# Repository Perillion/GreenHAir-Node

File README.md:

# GreenHAir Node

A Bluetooth Low Energy (BLE) Node based on the Nordic Semiconductor nRF54L series. Designed for environmental monitoring and efficient data transmission.

## Features

*   **Core:** Powered by the Nordic nRF54L series for ultra-low power consumption.
*   **Connectivity:** Bluetooth Low Energy (BLE) for reliable wireless communication.
*   **Modular Design:** Separate schematics for MCU, PSU, and Sensors for easy customization.
*   **Power Supply:** Optimized power management unit (`psu.kicad_sch`) powered by a CR2032 coin cell.
*   **Sensing:** Equipped with an AS7341DLG Lux sensor (I2C) for precise light measurement (`sensor.kicad_sch`).
*   **RF Performance:** Includes various antenna footprint options for optimal range.

## Hardware Structure

The project is divided into several KiCad schematics:

*   `GreenHAir_Node.kicad_sch`: Top-level hierarchy.
*   `mcu.kicad_sch`: Microcontroller and core logic.
*   `psu.kicad_sch`: Power supply and management.
*   `sensor.kicad_sch`: Sensor interfaces and components.

## Installation & Fabrication

### 1. PCB Fabrication
Generate the Gerber files from `GreenHAir_Node.kicad_pcb` and send them to your preferred PCB manufacturer.

### 2. Assembly
Follow the BOM (Bill of Materials) generated from the schematic to source and solder components.

### 3. Firmware
(Add instructions for flashing the nRF54L chip here)

## Customization

### Sensors
Currently populated with an AS7341DLG spectral sensor. The `sensor.kicad_sch` sheet allows for easy modification or expansion of the sensor array.

### Antenna
The design supports multiple antenna configurations found in the `libs/RF_Antenna.pretty` library.

## Contributing

Contributions are welcome! Please feel free to submit a Pull Request.

1.  Fork the repository
2.  Create your feature branch (`git checkout -b feature/AmazingFeature`)
3.  Commit your changes (`git commit -m 'Add some AmazingFeature'`)
4.  Push to the branch (`git push origin feature/AmazingFeature`)
5.  Open a Pull Request

## License

Distributed under the MIT License. See `LICENSE` for more information.

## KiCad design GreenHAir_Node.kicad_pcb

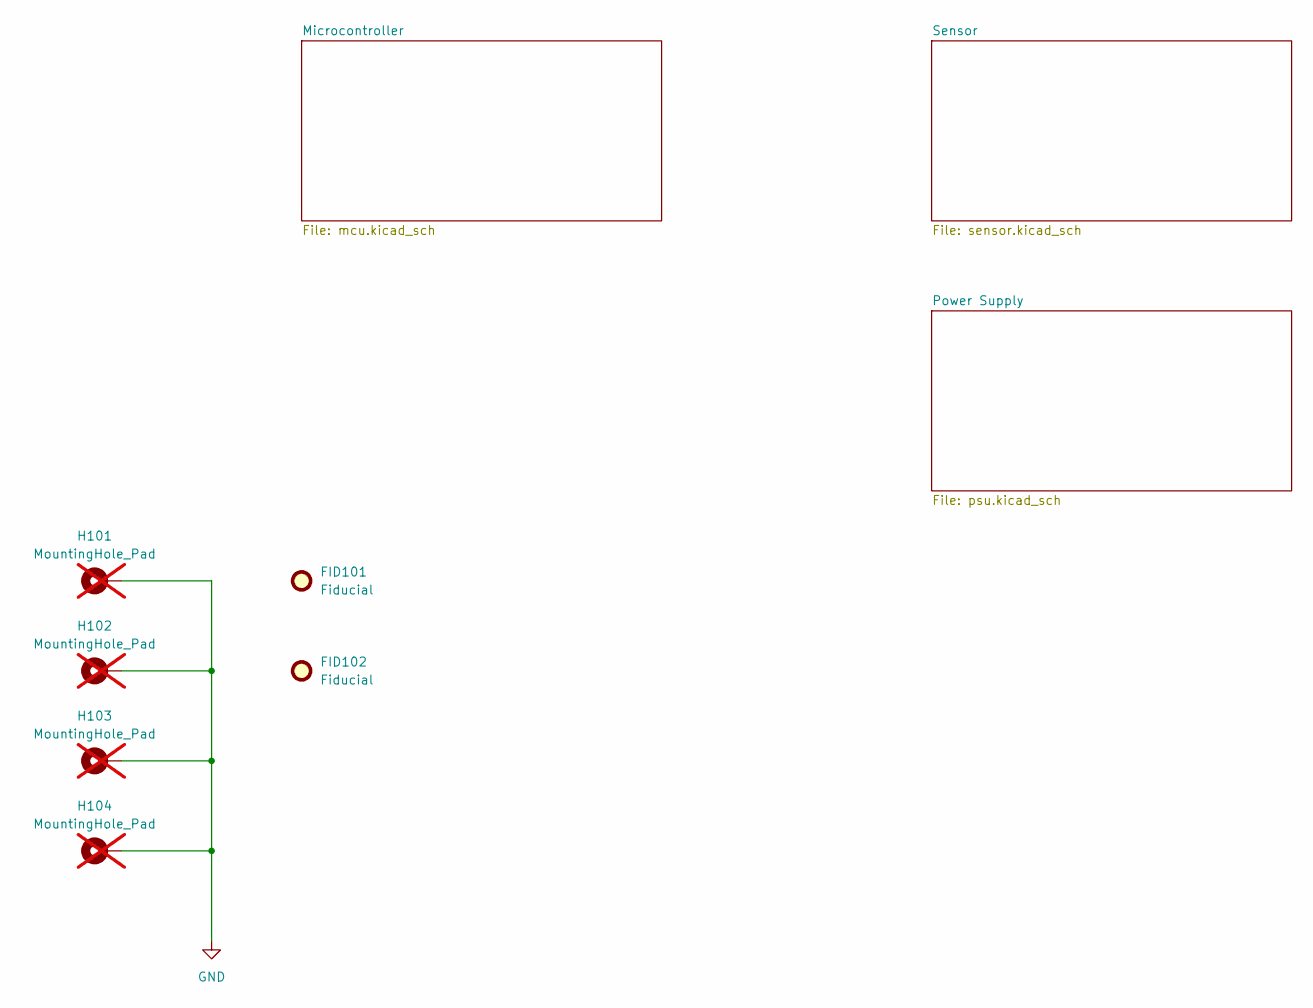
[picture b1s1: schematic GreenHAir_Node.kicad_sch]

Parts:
FID101, FID102: Fiducial; Fiducial_0.75mm_Mask1.5mm
H101, H102, H103, H104: MountingHole_Pad; MountingHole_2.7mm_M2.5_ISO14580_Pad_TopBottom; not fitted

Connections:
GND: H101.1, H102.1, H103.1, H104.1; also elsewhere on the board

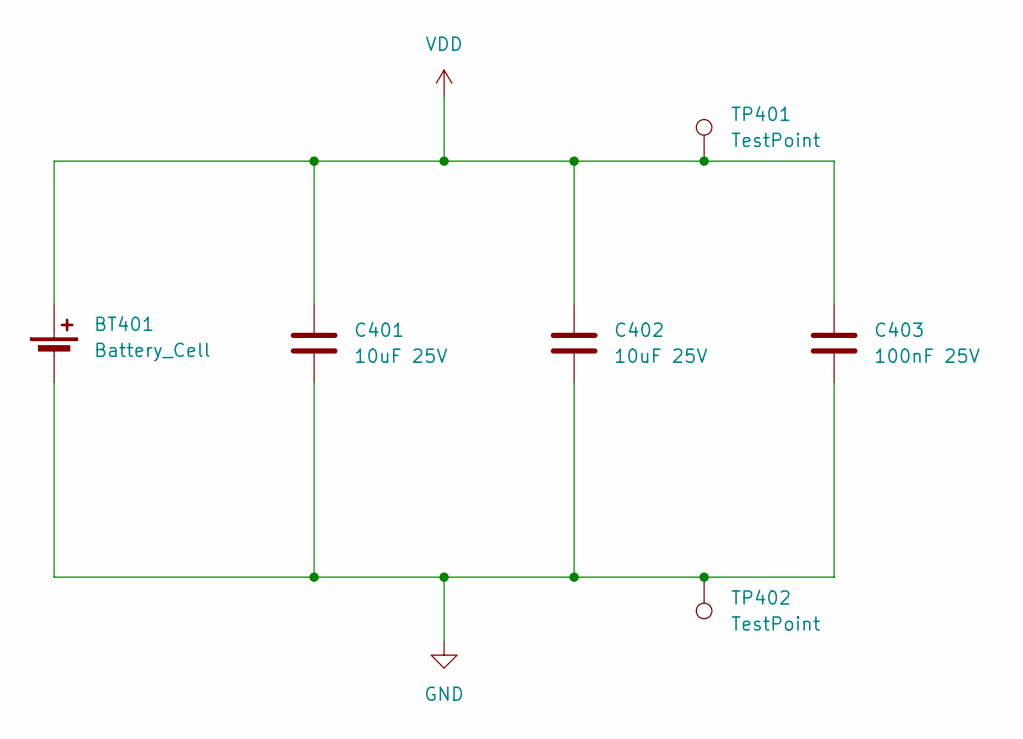
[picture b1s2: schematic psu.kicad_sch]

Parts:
BT401: Battery_Cell; BatteryHolder_Keystone_1058_1x2032
C401, C402: 10uF 25V; C_0603_1608Metric
C403: 100nF 25V; C_0402_1005Metric
TP401, TP402: TestPoint; TestPoint_Keystone_5005-5009_Compact

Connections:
GND: BT401.2 (-), C401.2, C402.2, C403.2, TP402.1; also elsewhere on the board
VDD: BT401.1 (+), C401.1, C402.1, C403.1, TP401.1; also elsewhere on the board

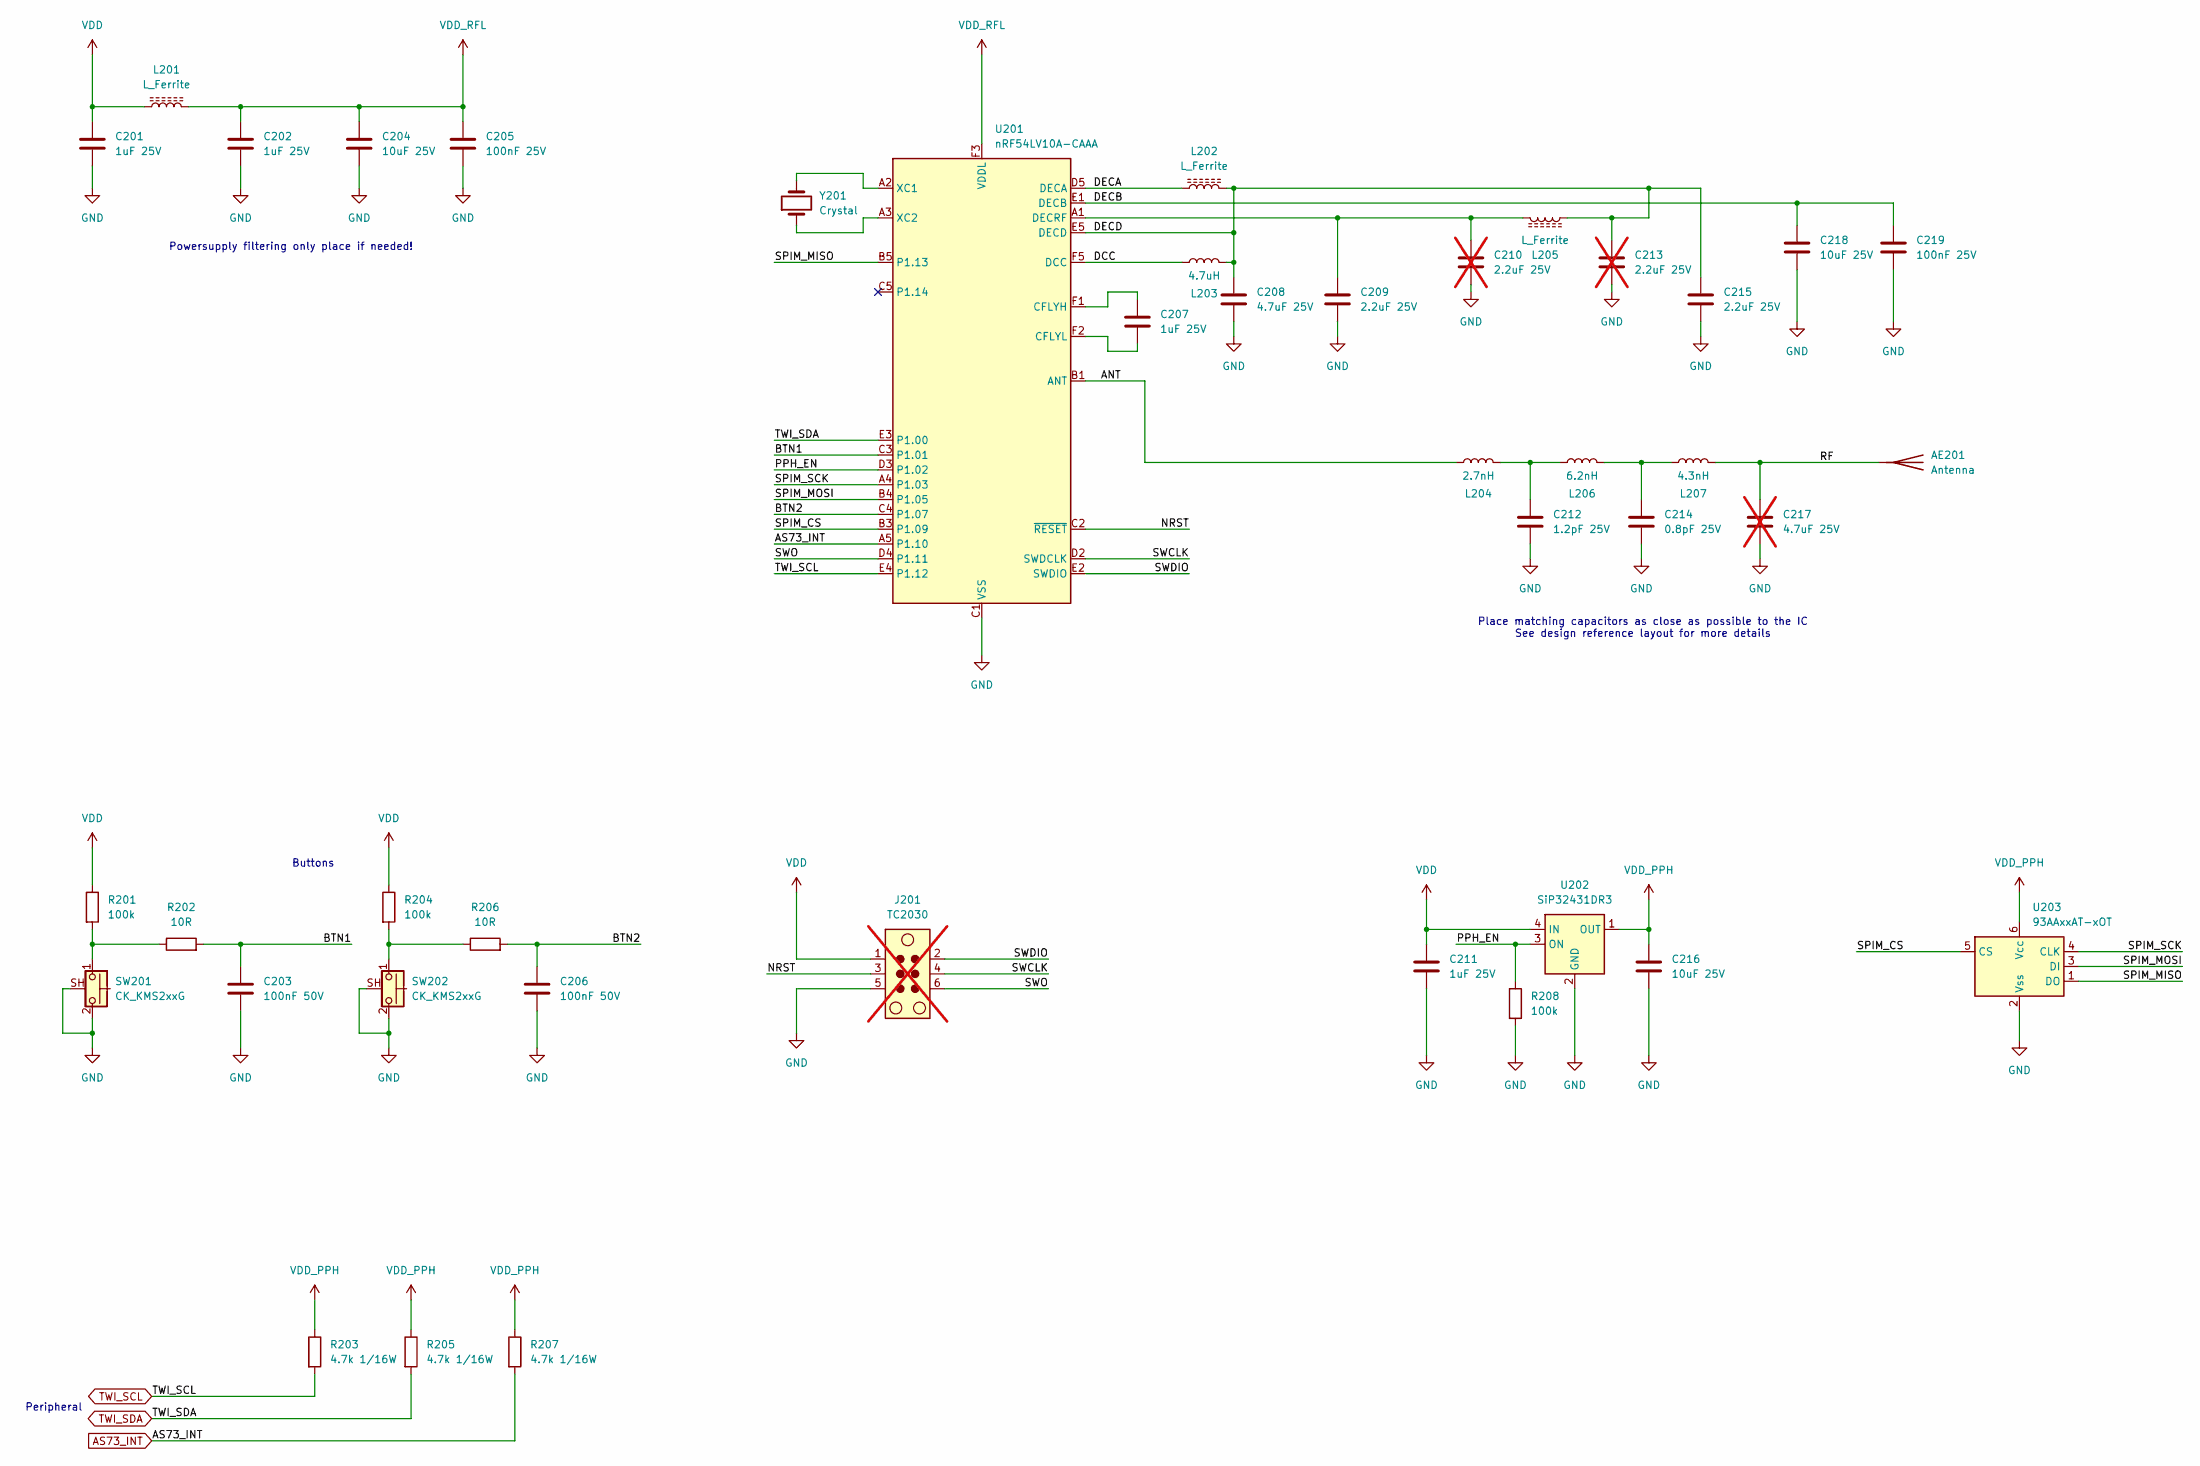
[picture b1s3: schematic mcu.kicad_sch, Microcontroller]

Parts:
AE201: Antenna; Texas_SWRA117D_2.4GHz_Left
C201, C202, C207: 1uF 25V; C_0603_1608Metric
C203, C206: 100nF 50V; C_0402_1005Metric
C204, C216, C218: 10uF 25V; C_0603_1608Metric
C205, C219: 100nF 25V; C_0402_1005Metric
C208: 4.7uF 25V; C_0603_1608Metric
C209, C215: 2.2uF 25V; C_0402_1005Metric
C210, C213: 2.2uF 25V; C_0402_1005Metric; not fitted
C211: 1uF 25V; C_0402_1005Metric
C212: 1.2pF 25V; C_0402_1005Metric
C214: 0.8pF 25V; C_0402_1005Metric
C217: 4.7uF 25V; C_0603_1608Metric; not fitted
J201: TC2030; Tag-Connect_TC2030-IDC-NL_2x03_P1.27mm_Vertical; not fitted
L201, L202, L205: L_Ferrite; L_0402_1005Metric
L203: 4.7uH; L_0402_1005Metric_Pad0.77x0.64mm_HandSolder
L204: 2.7nH; L_0402_1005Metric
L206: 6.2nH; L_0402_1005Metric
L207: 4.3nH; L_0402_1005Metric
R201, R204, R208: 100k; R_01005_0402Metric
R202, R206: 10R; R_01005_0402Metric
R203, R205, R207: 4.7k 1/16W; R_01005_0402Metric
SW201, SW202: CK_KMS2xxG; SW_SPST_CK_KMS2xxGP
U201: nRF54LV10A-CAAA; Nordic_CSP-29_1.9268x2.2893mm_Layout5x6_P0.35mm_Offcenter
U202: SiP32431DR3; SOT-363_SC-70-6
U203: 93AAxxAT-xOT; SOT-23-6
Y201: Crystal; Crystal_SMD_0603-2Pin_6.0x3.5mm_HandSoldering

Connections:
/Microcontroller/ANT: L204.1, U201.B1 (ANT)
/Microcontroller/BTN1: C203.1, R202.2, U201.C3 (P1.01)
/Microcontroller/BTN2: C206.1, R206.2, U201.C4 (P1.07)
/Microcontroller/DCC: L203.1, U201.F5 (DCC)
/Microcontroller/DECA: L202.1, U201.D5 (DECA)
/Microcontroller/DECB: C218.1, C219.1, U201.E1 (DECB)
/Microcontroller/DECD: C208.1, C213.1, C215.1, L202.2, L203.2, L205.2, U201.E5 (DECD)
/Microcontroller/NRST: J201.3, U201.C2 (~RESET)
/Microcontroller/PPH_EN: R208.1, U201.D3 (P1.02), U202.3 (ON)
/Microcontroller/RF: AE201.1 (A), C217.1, L207.2
/Microcontroller/SPIM_CS: U201.B3 (P1.09), U203.5 (CS)
/Microcontroller/SPIM_MISO: U201.B5 (P1.13), U203.1 (DO)
/Microcontroller/SPIM_MOSI: U201.B4 (P1.05), U203.3 (DI)
/Microcontroller/SPIM_SCK: U201.A4 (P1.03), U203.4 (CLK)
/Microcontroller/SWCLK: J201.4, U201.D2 (SWDCLK)
/Microcontroller/SWDIO: J201.2, U201.E2 (SWDIO)
/Microcontroller/SWO: J201.6, U201.D4 (P1.11)
AS73_INT: R207.2, U201.A5 (P1.10); also elsewhere on the board
GND: C201.2, C202.2, C203.2, C204.2, C205.2, C206.2, C208.2, C209.2, C210.2, C211.2, C212.2, C213.2, C214.2, C215.2, C216.2, C217.2, C218.2, C219.2, J201.5, R208.2, SW201.2, SW201.SH (B), SW202.2, SW202.SH (B), U201.C1 (VSS), U201.D1 (VSS), U201.F4 (VSS), U202.2 (GND), U202.5 (GND), U203.2 (Vss); also elsewhere on the board
unnamed: C212.1, L204.2, L206.1
unnamed: C214.1, L206.2, L207.1
unnamed: R201.2, R202.1, SW201.1
unnamed: R204.2, R206.1, SW202.1
unnamed: C207.1, U201.F1 (CFLYH)
unnamed: C207.2, U201.F2 (CFLYL)
unnamed: C209.1, C210.1, L205.1, U201.A1 (DECRF)
unnamed: U201.A2 (XC1), Y201.2
unnamed: U201.A3 (XC2), Y201.1
TWI_SCL: R203.2, U201.E4 (P1.12); also elsewhere on the board
TWI_SDA: R205.2, U201.E3 (P1.00); also elsewhere on the board
VDD: C201.1, C211.1, J201.1, L201.1, R201.1, R204.1, U202.4 (IN); also elsewhere on the board
VDD_PPH: C216.1, R203.1, R205.1, R207.1, U202.1 (OUT), U203.6 (Vcc); also elsewhere on the board
VDD_RFL: C202.1, C204.1, C205.1, L201.2, U201.F3 (VDDL)

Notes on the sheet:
Place matching capacitors as close as possible to the IC See design reference layout for more details
Powersupply filtering only place if needed!
Peripheral
Buttons

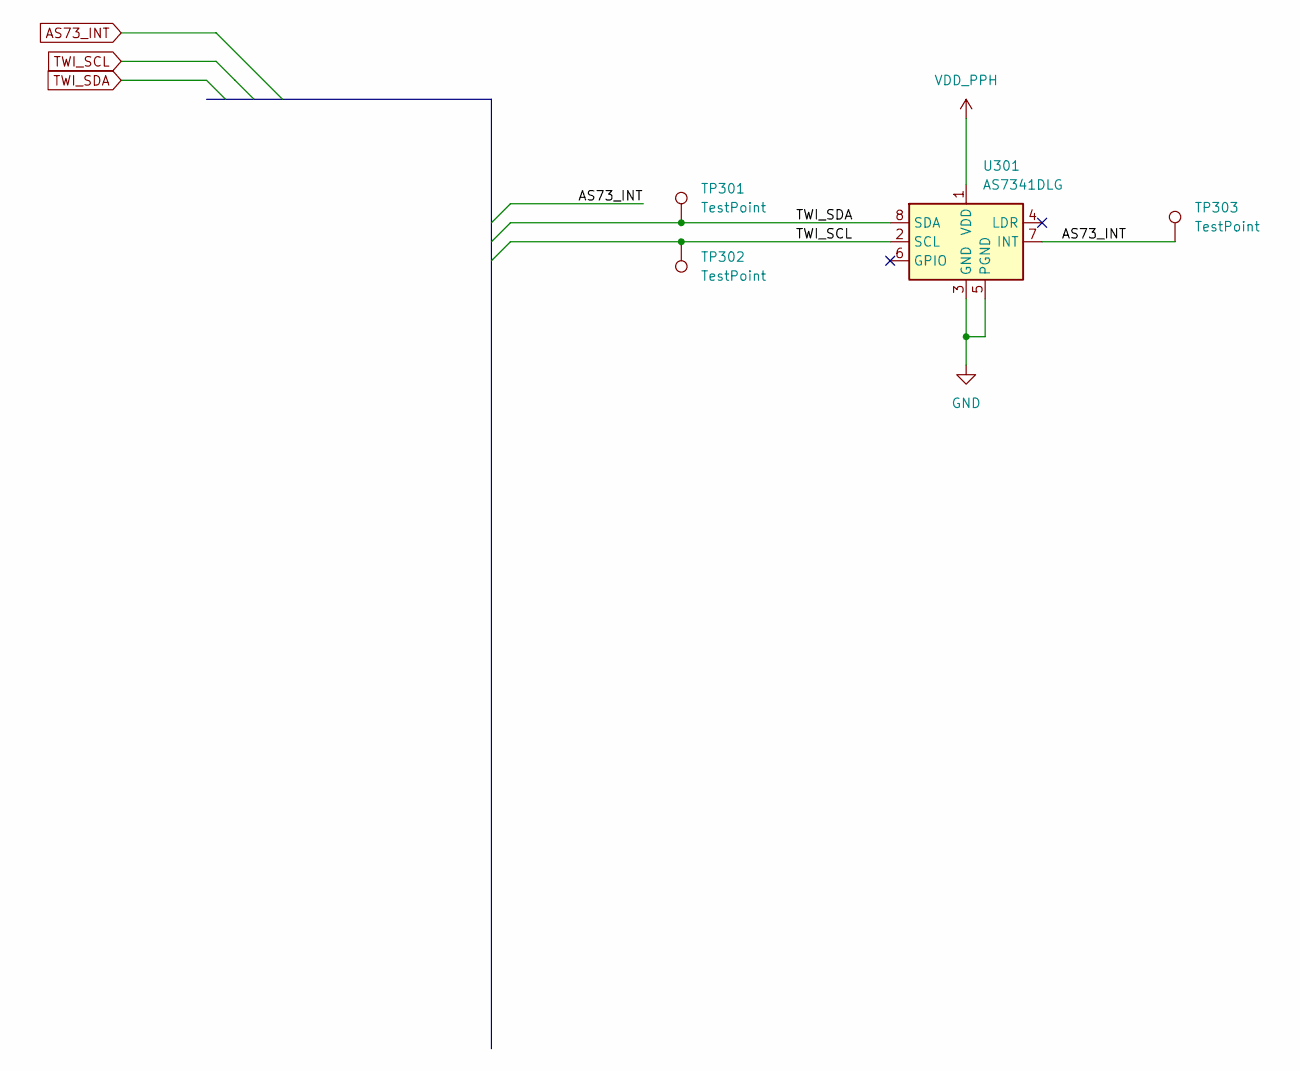
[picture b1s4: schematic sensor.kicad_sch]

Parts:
TP301, TP302, TP303: TestPoint; TestPoint_Keystone_5005-5009_Compact
U301: AS7341DLG; AMS_OLGA-8_2x3.1mm_P0.8mm

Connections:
AS73_INT: TP303.1, U301.7 (INT); also elsewhere on the board
GND: U301.3 (GND), U301.5 (PGND); also elsewhere on the board
TWI_SCL: TP302.1, U301.2 (SCL); also elsewhere on the board
TWI_SDA: TP301.1, U301.8 (SDA); also elsewhere on the board
VDD_PPH: U301.1 (VDD); also elsewhere on the board

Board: 2 copper layers, 58 parts (0 on the bottom side), 33 nets, no tracks yet.

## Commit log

2025-12-28 Add Project files to git.
2025-12-28 Add KiCAD gitignore
2025-12-28 Update .gitignore with KiCad exclusion rules
2025-12-28 worked on schematic
2026-01-01 Update Schematics - Add footprint to symbols.
2026-01-01 Update README.md to enhance project description and add contributing guidelines
2026-01-01 Update repo.

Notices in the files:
README.md:
License: MIT
